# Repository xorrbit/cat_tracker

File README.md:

# Cat Tracker

This Ardunio project reads location data from a GPS module and writes waypoints to a GPX file on a MicroSD card.

# A Bit More Technical info

This parses NMEA messages sent over a serial channel at 9600 bps. I've configured the NEO-7M to send out updates in low power mode at a rate of 1 Hz. It looks for GPRMC messages to get the lat/lon and date/time, and GPGSA messages to get the PDOP (position degree of precision) / HDOP (horizontal degree of precision) / VDOP (vertical degree of precision).

Once it has this info it creates a new file on the SD card, with the filename based on the date/time as DDHHMMSS.GPX, and starts writing GPX trkpt elements.

It was initially developed for the MSP430 microcontroller but the limited SRAM caused me to port it over to Arduino.

# Development
Since my GPS module/antenna (a uBlox NEO-7M) gets horrible reception indoors, I had to do most of my development and testing outside, so I set up a workstation on my balcony.

This was prototype #2 - switched to an Ardweeny on a breadboard instead of using a full Arduino.

This was prototype #3 - 3xAAA batteries for power, the Ardweeny and MicroSD card adapter (all soldered up), and the GPS module.

Prototype #3 but all taped up in a compact-ish package. SNES cart for scale. Weighs in at 85g or so, with 35g of that being the batteries.

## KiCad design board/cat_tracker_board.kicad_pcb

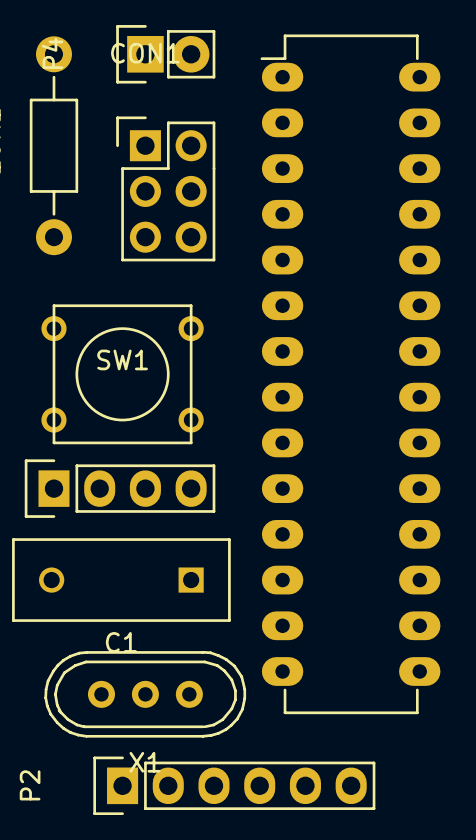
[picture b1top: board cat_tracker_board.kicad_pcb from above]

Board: 2 copper layers, 9 parts (0 on the bottom side), 10 nets, no tracks yet.

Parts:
10K1: R; Resistor_Horizontal_RM10mm
C1: 0.1u; C_Disc_D12_P7.75
CON1: AVR-ISP-6; Pin_Header_Straight_2x03
IC1: ATMEGA328-P; DIP-28_W7.62mm_LongPads
P1: GPS_NMEA; Pin_Header_Straight_1x04
P2: MicroSD Card Adapter; Pin_Header_Straight_1x06
P4: BATTERY; Pin_Header_Straight_1x02
SW1: RESET; SW_PUSH_SMALL
X1: 16Mhz XTAL; Crystal_HC49-U_Vertical_3Pin

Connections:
+BATT: 10K1.1, C1.1, CON1.2, IC1.7, IC1.20, IC1.21, P1.1, P2.5, P4.1
GND: C1.2, CON1.6, IC1.8, IC1.22, P1.4, P2.6, P4.2, SW1.2, X1.3
unnamed: 10K1.2, CON1.5, IC1.1, SW1.1
unnamed: CON1.1, IC1.18, P2.4
unnamed: CON1.3, CON1.4, IC1.19, P2.2
unnamed: IC1.9, X1.2
unnamed: IC1.10, X1.1
unnamed: IC1.15, P1.2
unnamed: IC1.16, P2.1
unnamed: IC1.17, P2.3

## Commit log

2016-08-20 Parse GPRMC messages from a GPS module for coords and output on serial port.
2016-08-20 Added NMEA message checksum checking and GPRMC valid fix checking.
2016-08-20 Changed output to GPX, added parsing of date and time info.
2016-08-21 Added SD card writing functionality.
2016-08-21 Tidied things up a tiny bit.
2016-08-21 Added proper GPX file footer.
2016-08-21 Added KiCad project files.
2016-08-21 Added atmega pins and gps pinout, fixed weird bug with Ardweeny.
2016-08-21 Added parsing of accuracy info from GPGSA messages and output to GPX trkpts.
2016-08-21 Added a bit of power saving stuff.
2016-08-22 Revert "Added a bit of power saving stuff."
    This reverts commit d84dd544aa0162d0f8ebcea1a0d198b9f4bdbec6.
2016-08-22 Reworked schematic with xtal.
2016-08-22 First pass at a through-hole board layout.
2016-08-22 Added todo.md.
